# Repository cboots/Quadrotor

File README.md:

Quadrotor
======

This project contains all the schematics, code, documentation and CAD files for my quadrotor designs.

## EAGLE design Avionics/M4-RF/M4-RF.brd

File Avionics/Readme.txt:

This folder holds all of the electronics designs for the quads

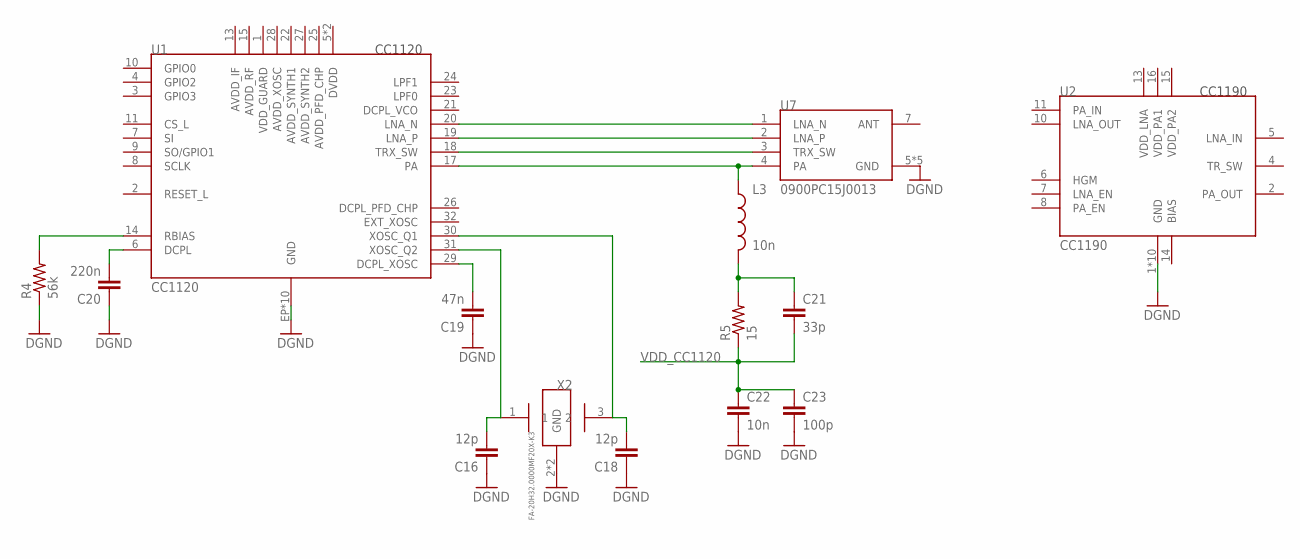
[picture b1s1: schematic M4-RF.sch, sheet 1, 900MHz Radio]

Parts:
C16, C18: 12p; 0402-CAP
C19: 47n; 0402-CAP
C20: 220n; 0402-CAP
C21: 33p; 0402-CAP
C22: 10n; 0402-CAP
C23: 100p; 0402-CAP
L3: 10n; C0402
R4: 56k; 0402-RES
R5: 15; 0402-RES
U1: CC1120; RHB_S-PVQFN-N32
U2: CC1190; RGV_S-PVQFN-N16
U7: 0900PC15J0013
X2: FA-20H32.0000MF20X-K3; FA-20H

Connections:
GND: C16.1, C18.1, C19.1, C20.1, C22.2, C23.2, R4.1, U1.EP (GND), U1.EXP@1 (GND), U1.EXP@2 (GND), U1.EXP@3 (GND), U1.EXP@4 (GND), U1.EXP@5 (GND), U1.EXP@6 (GND), U1.EXP@7 (GND), U1.EXP@8 (GND), U1.EXP@9 (GND), U2.1 (GND), U2.3 (GND), U2.9 (GND), U2.12 (GND), U2.EP (GND), U2.EP@1 (GND), U2.EP@2 (GND), U2.EP@3 (GND), U2.EP@4 (GND), U2.EP@5 (GND), U7.5 (GND), U7.6 (GND), U7.8 (GND), U7.9 (GND), U7.10 (GND), X2.2 (GND), X2.4 (GND); also elsewhere on the board
unnamed: C16.2, U1.31 (XOSC_Q2), X2.1
unnamed: C18.2, U1.30 (XOSC_Q1), X2.3 (2)
unnamed: C19.2, U1.29 (DCPL_XOSC)
unnamed: C20.2, U1.6 (DCPL)
unnamed: R4.2, U1.14 (RBIAS)
unnamed: U1.20 (LNA_N), U7.1 (LNA_N)
unnamed: U1.19 (LNA_P), U7.2 (LNA_P)
unnamed: U1.18 (TRX_SW), U7.3 (TRX_SW)
unnamed: L3.1, U1.17 (PA), U7.4 (PA)
unnamed: C21.1, L3.2, R5.2
VDD_CC1120: C21.2, C22.1, C23.1, R5.1

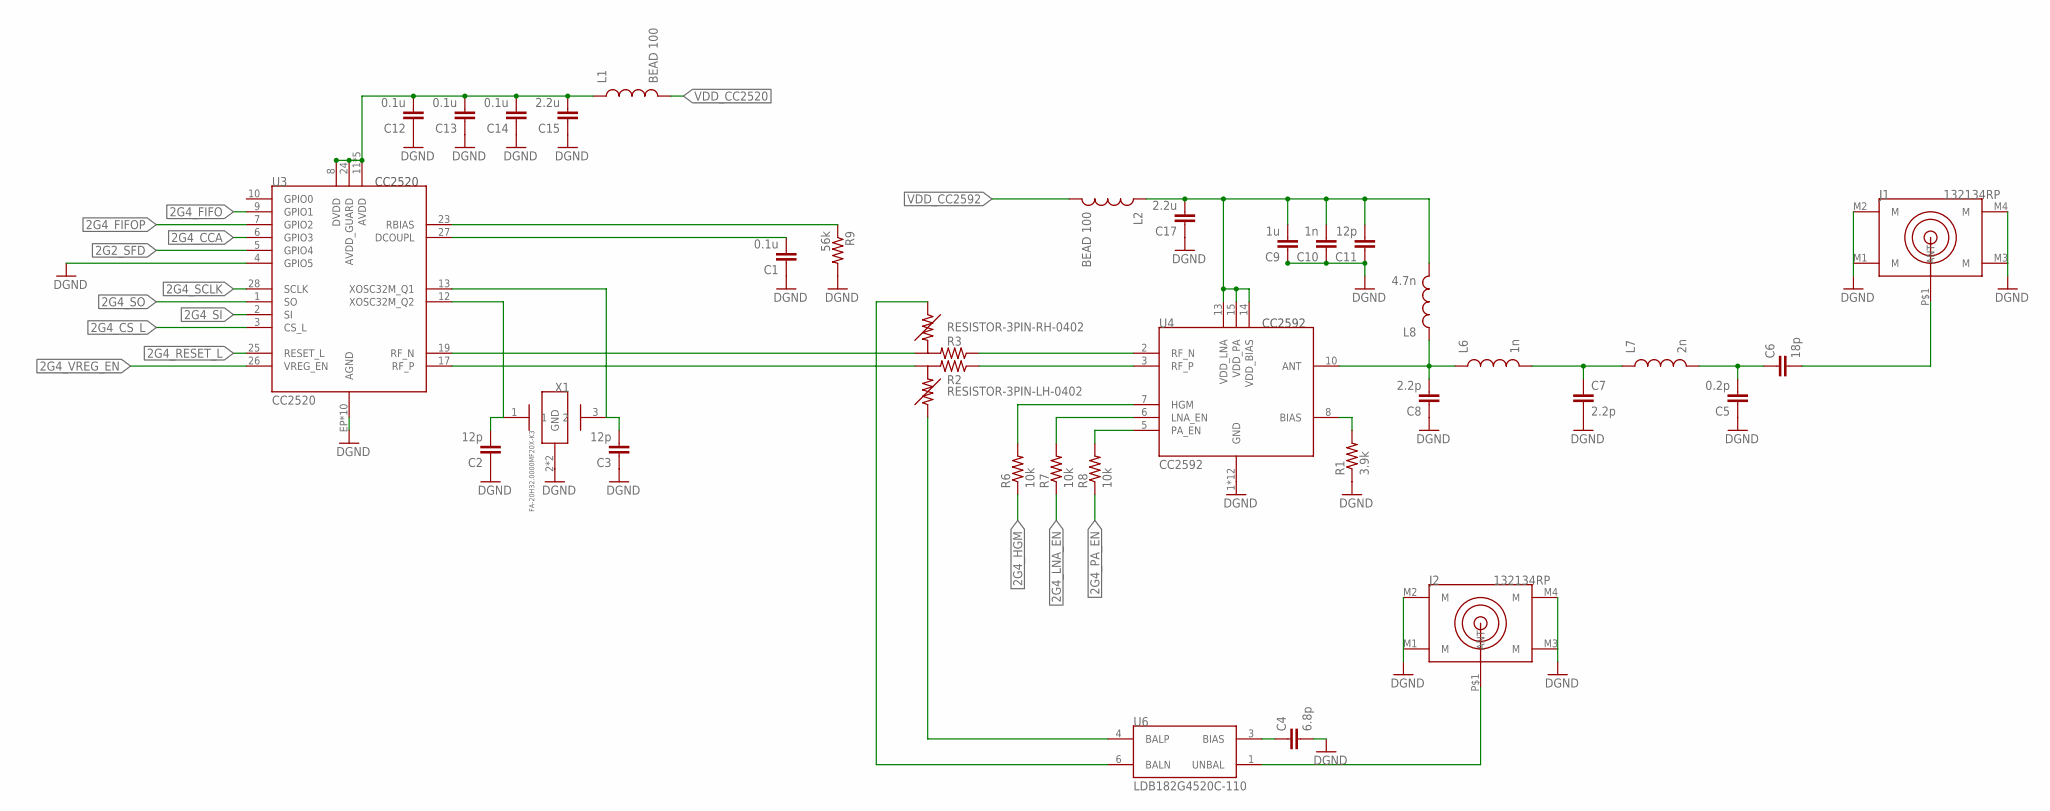
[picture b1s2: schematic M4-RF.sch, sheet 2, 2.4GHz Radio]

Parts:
C1, C12, C13, C14: 0.1u; 0402-CAP
C2, C3, C11: 12p; 0402-CAP
C4: 6.8p; 0402-CAP
C5: 0.2p; 0402-CAP
C6: 18p; 0402-CAP
C7, C8: 2.2p; 0402-CAP
C9: 1u; 0402-CAP
C10: 1n; 0402-CAP
C15, C17: 2.2u; 0402-CAP
J1, J2: 132134RP; RP-SMA-TH
L1, L2: BEAD 100; C0402
L6: 1n; C0402
L7: 2n; C0402
L8: 4.7n; C0402
R1: 3.9k; 0402-RES
R2: RESISTOR-3PIN-LH-0402; 0402-RES-3PIN-LH
R3: RESISTOR-3PIN-RH-0402; 0402-RES-3PIN-RH
R6, R7, R8: 10k; 0402-RES
R9: 56k; 0402-RES
U3: CC2520; RHD_S-PVQFN-N28
U4: CC2592; RGV_S-PVQFN-N16
U6: LDB182G4520C-110; LDB18
X1: FA-20H32.0000MF20X-K3; FA-20H

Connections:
2G2_SFD: U3.5 (GPIO4)
2G4_CCA: U3.6 (GPIO3)
2G4_CS_L: U3.3 (CS_L)
2G4_FIFO: U3.9 (GPIO1)
2G4_FIFOP: U3.7 (GPIO2)
2G4_HGM: R6.1
2G4_LG: C6.2, J1.P$1 (ANT)
2G4_LNA_EN: R7.1
2G4_LP: J2.P$1 (ANT), U6.1 (UNBAL)
2G4_PA_EN: R8.1
2G4_RESET_L: U3.25 (RESET_L)
2G4_SCLK: U3.28 (SCLK)
2G4_SI: U3.2 (SI)
2G4_SO: U3.1 (SO)
2G4_VREG_EN: U3.26 (VREG_EN)
GND: C1.1, C2.1, C3.1, C4.2, C5.1, C7.2, C8.1, C9.1, C10.1, C11.1, C12.1, C13.1, C14.1, C15.1, C17.1, J1.M1 (M), J1.M2 (M), J1.M3 (M), J1.M4 (M), J2.M1 (M), J2.M2 (M), J2.M3 (M), J2.M4 (M), R1.1, R9.2, U3.4 (GPIO5), U3.EP (AGND), U3.EXP@1 (AGND), U3.EXP@2 (AGND), U3.EXP@3 (AGND), U3.EXP@4 (AGND), U3.EXP@5 (AGND), U3.EXP@6 (AGND), U3.EXP@7 (AGND), U3.EXP@8 (AGND), U3.EXP@9 (AGND), U4.1 (GND), U4.4 (GND), U4.9 (GND), U4.11 (GND), U4.12 (GND), U4.16 (GND), U4.EP (GND), U4.EP@1 (GND), U4.EP@2 (GND), U4.EP@3 (GND), U4.EP@4 (GND), U4.EP@5 (GND), X1.2 (GND), X1.4 (GND); also elsewhere on the board
unnamed: R3.2, U3.19 (RF_N)
unnamed: R2.2, U3.17 (RF_P)
unnamed: R6.2, U4.7 (HGM)
unnamed: R7.2, U4.6 (LNA_EN)
unnamed: R2.1, U4.3 (RF_P)
unnamed: C8.2, L6.1, L8.1, U4.10 (ANT)
unnamed: C7.1, L6.2, L7.1
unnamed: C5.2, C6.1, L7.2
unnamed: C9.2, C10.2, C11.2, C17.2, L2.1, L8.2, U4.13 (VDD_LNA), U4.14 (VDD_BIAS), U4.15 (VDD_PA)
unnamed: R1.2, U4.8 (BIAS)
unnamed: R3.1, U4.2 (RF_N)
unnamed: R8.2, U4.5 (PA_EN)
unnamed: C12.2, C13.2, C14.2, C15.2, L1.1, U3.8 (DVDD), U3.11 (AVDD), U3.14 (AVDD), U3.16 (AVDD), U3.20 (AVDD), U3.22 (AVDD), U3.24 (AVDD_GUARD)
unnamed: C2.2, U3.12 (XOSC32M_Q2), X1.1
unnamed: R9.1, U3.23 (RBIAS)
unnamed: C1.2, U3.27 (DCOUPL)
unnamed: C3.2, U3.13 (XOSC32M_Q1), X1.3 (2)
unnamed: R2.3, U6.4 (BALP)
unnamed: R3.3, U6.6 (BALN)
unnamed: C4.1, U6.3 (BIAS)
VDD_CC2520: L1.2
VDD_CC2592: L2.2

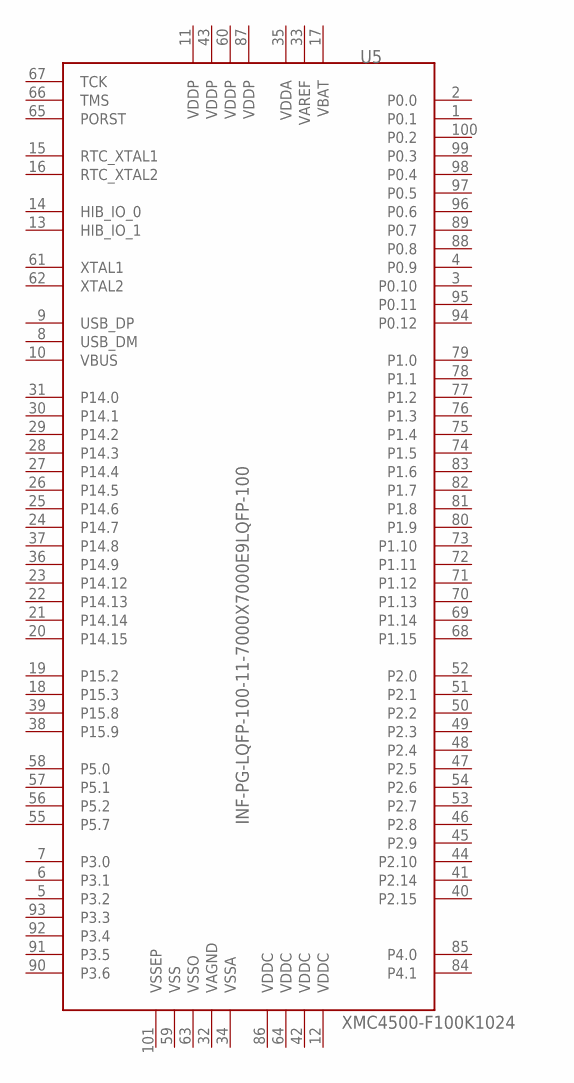
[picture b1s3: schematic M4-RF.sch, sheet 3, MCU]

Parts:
U5: INF-PG-LQFP-100-11-7000X7000E9LQFP-100; INF-PG-LQFP-100-11-7000X7000E9PRIMARY

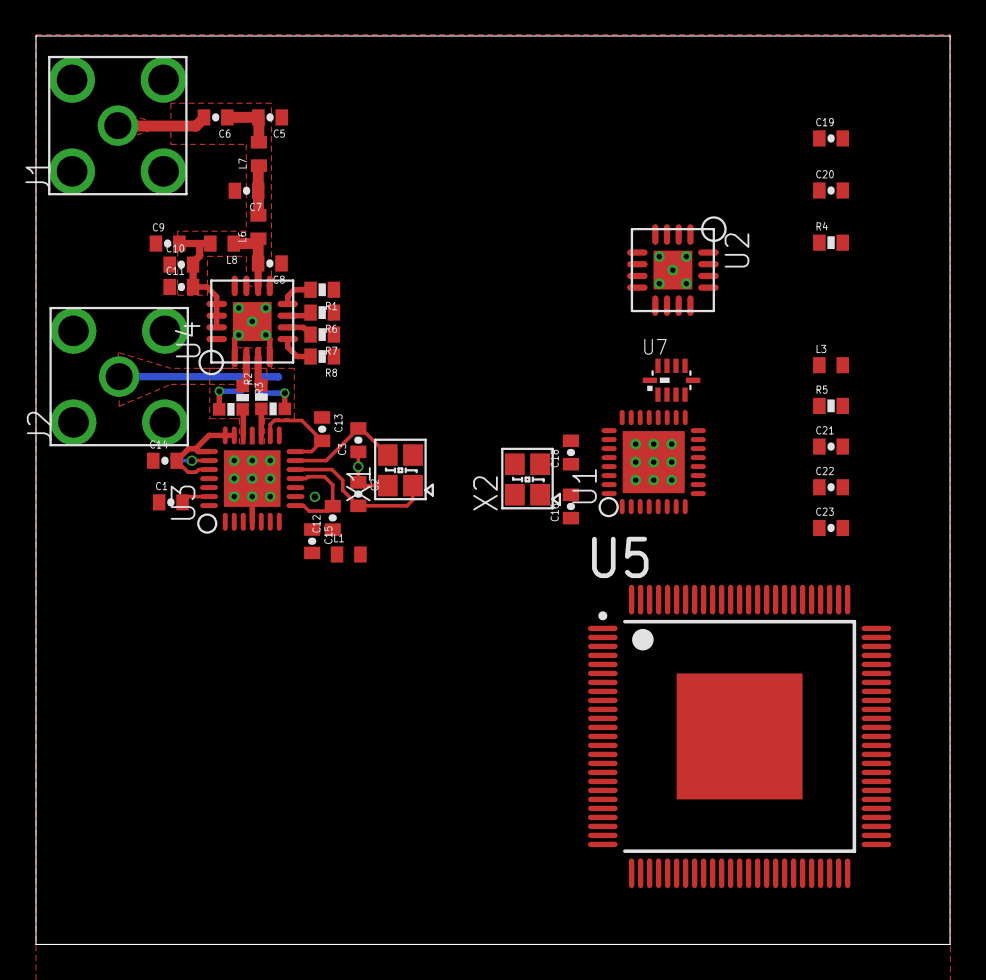
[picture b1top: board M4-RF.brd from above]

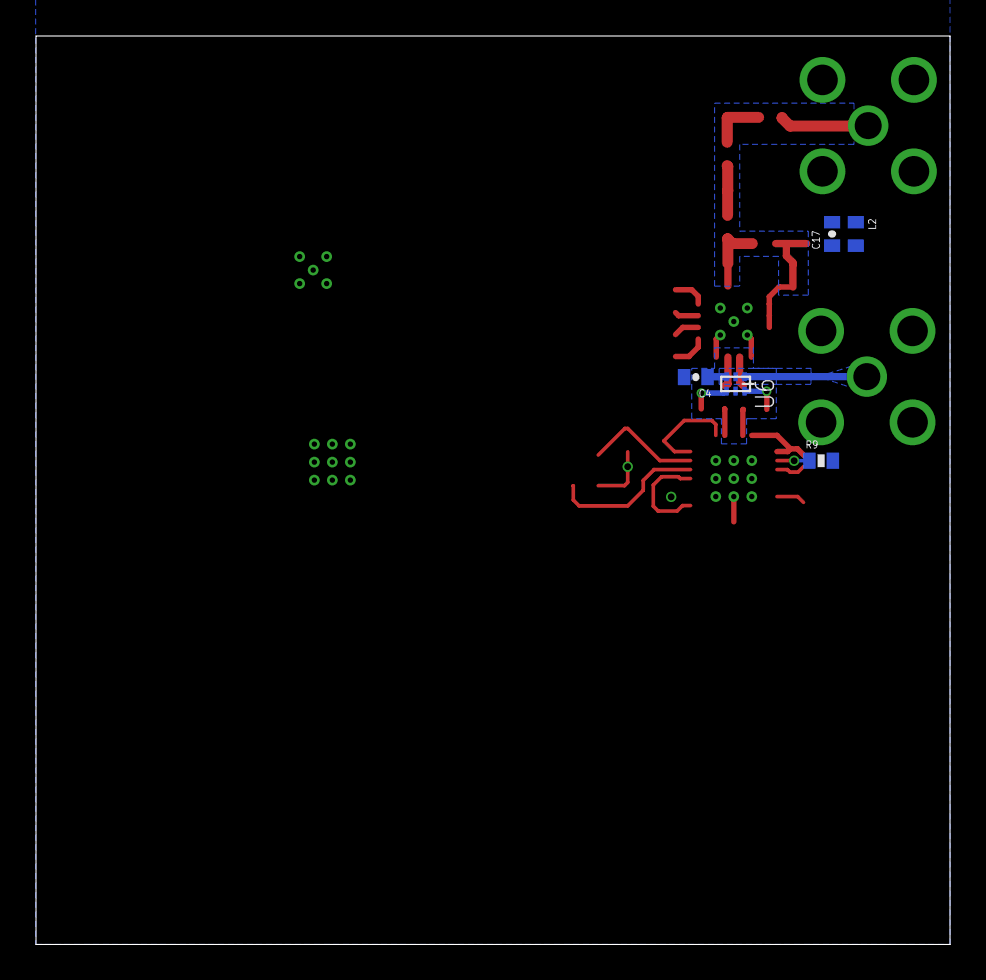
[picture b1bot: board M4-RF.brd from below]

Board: 4 copper layers, 50.8 x 50.5 mm, 49 parts (5 on the bottom side), 34 nets.

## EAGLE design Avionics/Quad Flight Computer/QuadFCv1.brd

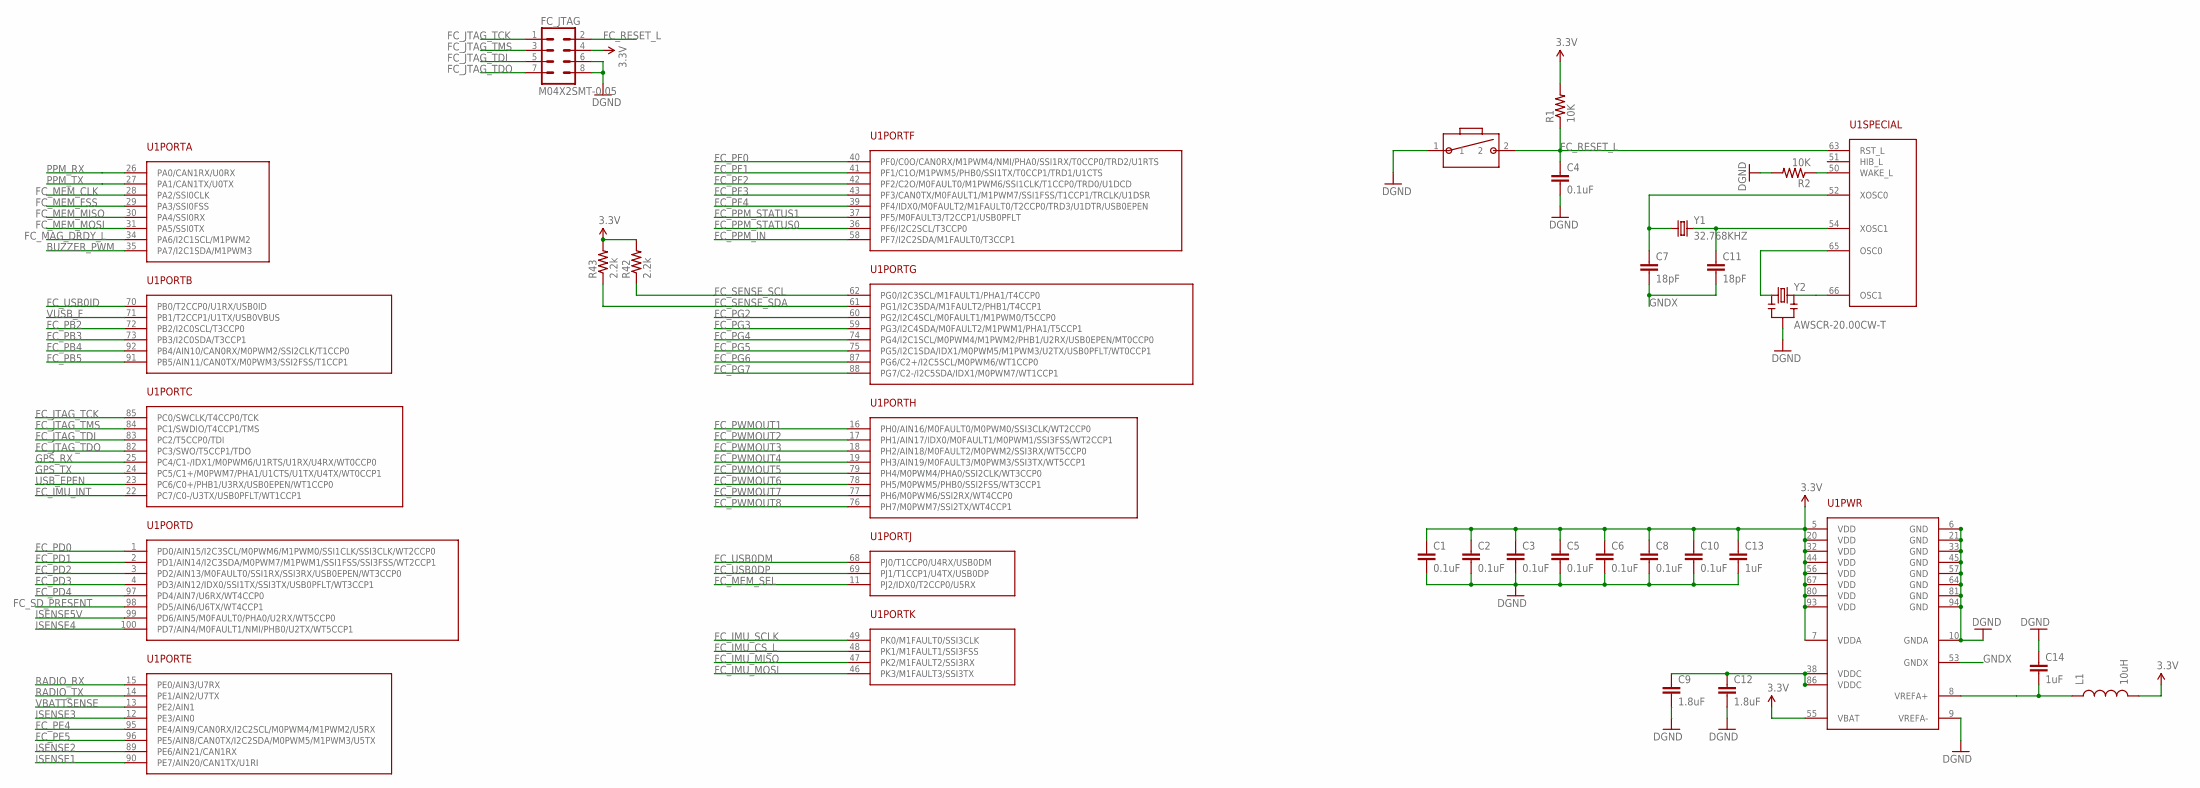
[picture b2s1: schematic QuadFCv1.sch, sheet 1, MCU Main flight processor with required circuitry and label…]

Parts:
C1, C2, C3, C4, C5, C6, C8, C10: 0.1uF; 0402-CAP
C7, C11: 18pF; 0402-CAP
C9, C12: 1.8uF; 0402-CAP
C13, C14: 1uF; 0402-CAP
FC_JTAG: M04X2SMT-0.05; 2X4_SMT-0.05
L1: 10uH; 0603
R1, R2: 10K; 0402-RES
R42, R43: 2.2k; 0402-RES
SW1: PTS635VL31-VERT; PTS635VL31
U1: TM4C123GH6PZ; LQFP100
Y1: 32.768KHZ; ECS-.327-12.5-34B
Y2: AWSCR-20.00CW-T; AWSCR-CW

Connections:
3.3V: C1.1, C2.1, C3.1, C5.1, C6.1, C8.1, C10.1, C13.1, FC_JTAG.4, L1.2, R1.2, R42.2, R43.2, U1.5 (VDD), U1.7 (VDDA), U1.20 (VDD), U1.32 (VDD), U1.44 (VDD), U1.55 (VBAT), U1.56 (VDD), U1.67 (VDD), U1.80 (VDD), U1.93 (VDD); also elsewhere on the board
BUZZER_PWM: U1.35 (PA7/I2C1SDA/M1PWM3); also elsewhere on the board
FC_IMU_CS_L: U1.48 (PK1/M1FAULT1/SSI3FSS); also elsewhere on the board
FC_IMU_INT: U1.22 (PC7/C0-/U3TX/USB0PFLT/WT1CCP1); also elsewhere on the board
FC_IMU_MISO: U1.47 (PK2/M1FAULT2/SSI3RX); also elsewhere on the board
FC_IMU_MOSI: U1.46 (PK3/M1FAULT3/SSI3TX); also elsewhere on the board
FC_IMU_SCLK: U1.49 (PK0/M1FAULT0/SSI3CLK); also elsewhere on the board
FC_JTAG_TCK: FC_JTAG.1, U1.85 (PC0/SWCLK/T4CCP0/TCK); also elsewhere on the board
FC_JTAG_TDI: FC_JTAG.5, U1.83 (PC2/T5CCP0/TDI); also elsewhere on the board
FC_JTAG_TDO: FC_JTAG.7, U1.82 (PC3/SWO/T5CCP1/TDO); also elsewhere on the board
FC_JTAG_TMS: FC_JTAG.3, U1.84 (PC1/SWDIO/T4CCP1/TMS); also elsewhere on the board
FC_MAG_DRDY_L: U1.34 (PA6/I2C1SCL/M1PWM2); also elsewhere on the board
FC_MEM_CLK: U1.28 (PA2/SSI0CLK); also elsewhere on the board
FC_MEM_FSS: U1.29 (PA3/SSI0FSS); also elsewhere on the board
FC_MEM_MISO: U1.30 (PA4/SSI0RX); also elsewhere on the board
FC_MEM_MOSI: U1.31 (PA5/SSI0TX); also elsewhere on the board
FC_MEM_SEL: U1.11 (PJ2/IDX0/T2CCP0/U5RX); also elsewhere on the board
FC_PB2: U1.72 (PB2/I2C0SCL/T3CCP0); also elsewhere on the board
FC_PB3: U1.73 (PB3/I2C0SDA/T3CCP1); also elsewhere on the board
FC_PB4: U1.92 (PB4/AIN10/CAN0RX/M0PWM2/SSI2CLK/T1CCP0); also elsewhere on the board
FC_PB5: U1.91 (PB5/AIN11/CAN0TX/M0PWM3/SSI2FSS/T1CCP1); also elsewhere on the board
FC_PD0: U1.1 (PD0/AIN15/I2C3SCL/M0PWM6/M1PWM0/SSI1CLK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); also elsewhere on the board
FC_PD1: U1.2 (PD1/AIN14/I2C3SDA/M0PWM7/M1PWM1/SSI1FSS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); also elsewhere on the board
FC_PD2: U1.3 (PD2/AIN13/M0FAULT0/SSI1RX/SSI3RX/USB0EP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); also elsewhere on the board
FC_PD3: U1.4 (PD3/AIN12/IDX0/SSI1TX/SSI3TX/USB0PFLT/W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); also elsewhere on the board
FC_PD4: U1.97 (PD4/AIN7/U6RX/WT4CCP0); also elsewhere on the board
FC_PE4: U1.95 (PE4/AIN9/CAN0RX/I2C2SCL/M0PWM4/M1PWM2/U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); also elsewhere on the board
FC_PE5: U1.96 (PE5/AIN8/CAN0TX/I2C2SDA/M0PWM5/M1PWM3/U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); also elsewhere on the board
FC_PF0: U1.40 (PF0/C0O/CAN0RX/M1PWM4/NMI/PHA0/SSI1RX/T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); also elsewhere on the board
FC_PF1: U1.41 (PF1/C1O/M1PWM5/PHB0/SSI1TX/T0CCP1/TRD1/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); also elsewhere on the board
FC_PF2: U1.42 (PF2/C2O/M0FAULT0/M1PWM6/SSI1CLK/T1CCP0/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); also elsewhere on the board
FC_PF3: U1.43 (PF3/CAN0TX/M0FAULT1/M1PWM7/SSI1FSS/T1CC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); also elsewhere on the board
FC_PF4: U1.39 (PF4/IDX0/M0FAULT2/M1FAULT0/T2CCP0/TRD3/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); also elsewhere on the board
FC_PG2: U1.60 (PG2/I2C4SCL/M0FAULT1/M1PWM0/T5CCP0); also elsewhere on the board
FC_PG3: U1.59 (PG3/I2C4SDA/M0FAULT2/M1PWM1/PHA1/T5CCP1); also elsewhere on the board
FC_PG4: U1.74 (PG4/I2C1SCL/M0PWM4/M1PWM2/PHB1/U2RX/USB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); also elsewhere on the board
FC_PG5: U1.75 (PG5/I2C1SDA/IDX1/M0PWM5/M1PWM3/U2TX/USB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); also elsewhere on the board
FC_PG6: U1.87 (PG6/C2+/I2C5SCL/M0PWM6/WT1CCP0); also elsewhere on the board
FC_PG7: U1.88 (PG7/C2-/I2C5SDA/IDX1/M0PWM7/WT1CCP1); also elsewhere on the board
FC_PPM_IN: U1.58 (PF7/I2C2SDA/M1FAULT0/T3CCP1); also elsewhere on the board
FC_PPM_STATUS0: U1.36 (PF6/I2C2SCL/T3CCP0); also elsewhere on the board
FC_PPM_STATUS1: U1.37 (PF5/M0FAULT3/T2CCP1/USB0PFLT); also elsewhere on the board
FC_PWMOUT1: U1.16 (PH0/AIN16/M0FAULT0/M0PWM0/SSI3CLK/WT2CC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); also elsewhere on the board
FC_PWMOUT2: U1.17 (PH1/AIN17/IDX0/M0FAULT1/M0PWM1/SSI3FSS/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); also elsewhere on the board
FC_PWMOUT3: U1.18 (PH2/AIN18/M0FAULT2/M0PWM2/SSI3RX/WT5CCP0); also elsewhere on the board
FC_PWMOUT4: U1.19 (PH3/AIN19/M0FAULT3/M0PWM3/SSI3TX/WT5CCP1); also elsewhere on the board
FC_PWMOUT5: U1.79 (PH4/M0PWM4/PHA0/SSI2CLK/WT3CCP0); also elsewhere on the board
FC_PWMOUT6: U1.78 (PH5/M0PWM5/PHB0/SSI2FSS/WT3CCP1); also elsewhere on the board
FC_PWMOUT7: U1.77 (PH6/M0PWM6/SSI2RX/WT4CCP0); also elsewhere on the board
FC_PWMOUT8: U1.76 (PH7/M0PWM7/SSI2TX/WT4CCP1); also elsewhere on the board
FC_RESET_L: C4.1, FC_JTAG.2, R1.1, SW1.2, U1.63 (RST_L); also elsewhere on the board
FC_SD_PRESENT: U1.98 (PD5/AIN6/U6TX/WT4CCP1); also elsewhere on the board
FC_SENSE_SCL: R42.1, U1.62 (PG0/I2C3SCL/M1FAULT1/PHA1/T4CCP0); also elsewhere on the board
FC_SENSE_SDA: R43.1, U1.61 (PG1/I2C3SDA/M1FAULT2/PHB1/T4CCP1); also elsewhere on the board
FC_USB0DM: U1.68 (PJ0/T1CCP0/U4RX/USB0DM); also elsewhere on the board
FC_USB0DP: U1.69 (PJ1/T1CCP1/U4TX/USB0DP); also elsewhere on the board
FC_USB0ID: U1.70 (PB0/T2CCP0/U1RX/USB0ID); also elsewhere on the board
GND: C1.2, C2.2, C3.2, C4.2, C5.2, C6.2, C8.2, C9.2, C10.2, C12.2, C13.2, C14.1, FC_JTAG.6, FC_JTAG.8, R2.2, SW1.1, U1.6 (GND), U1.9 (VREFA-), U1.10 (GNDA), U1.21 (GND), U1.33 (GND), U1.45 (GND), U1.57 (GND), U1.64 (GND), U1.81 (GND), U1.94 (GND), Y2.P$2 (2); also elsewhere on the board
GNDX: C7.2, C11.2, U1.53 (GNDX)
GPS_RX: U1.25 (PC4/C1-/IDX1/M0PWM6/U1RTS/U1RX/U4RX/WT0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); also elsewhere on the board
GPS_TX: U1.24 (PC5/C1+/M0PWM7/PHA1/U1CTS/U1TX/U4TX/WT0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); also elsewhere on the board
ISENSE1: U1.90 (PE7/AIN20/CAN1TX/U1RI); also elsewhere on the board
ISENSE2: U1.89 (PE6/AIN21/CAN1RX); also elsewhere on the board
ISENSE3: U1.12 (PE3/AIN0); also elsewhere on the board
ISENSE4: U1.100 (PD7/AIN4/M0FAULT1/NMI/PHB0/U2TX/WT5CCP1); also elsewhere on the board
ISENSE5V: U1.99 (PD6/AIN5/M0FAULT0/PHA0/U2RX/WT5CCP0); also elsewhere on the board
unnamed: C14.2, L1.1, U1.8 (VREFA+)
unnamed: C9.1, C12.1, U1.38 (VDDC), U1.86 (VDDC)
unnamed: C11.1, U1.54 (XOSC1), Y1.P$2 (2)
unnamed: C7.1, U1.52 (XOSC0), Y1.P$1 (1)
unnamed: R2.1, U1.50 (WAKE_L)
unnamed: U1.65 (OSC0), Y2.P$1 (1)
unnamed: U1.66 (OSC1), Y2.P$3 (3)
PPM_RX: U1.26 (PA0/CAN1RX/U0RX); also elsewhere on the board
PPM_TX: U1.27 (PA1/CAN1TX/U0TX); also elsewhere on the board
RADIO_RX: U1.15 (PE0/AIN3/U7RX); also elsewhere on the board
RADIO_TX: U1.14 (PE1/AIN2/U7TX); also elsewhere on the board
USB_EPEN: U1.23 (PC6/C0+/PHB1/U3RX/USB0EPEN/WT1CCP0); also elsewhere on the board
VBATTSENSE: U1.13 (PE2/AIN1); also elsewhere on the board
VUSB_F: U1.71 (PB1/T2CCP1/U1TX/USB0VBUS); also elsewhere on the board

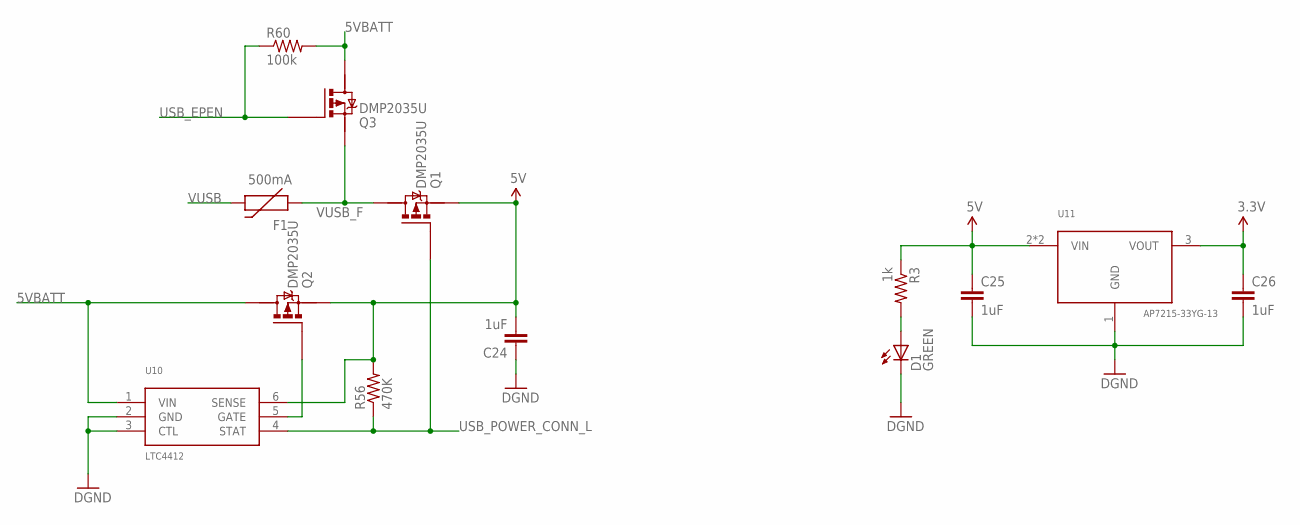
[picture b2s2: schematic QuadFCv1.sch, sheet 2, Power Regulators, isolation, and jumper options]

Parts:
C24, C25, C26: 1uF; 0402-CAP
D1: GREEN; LED-0603
F1: 500mA; PTC-1206
Q1, Q2, Q3: DMP2035U; SOT23
R3: 1k; 0402-RES
R56: 470K; 0402-RES
R60: 100k; 0402-RES
U10: LTC4412; SOT23-6
U11: AP7215-33YG-13; SOT89

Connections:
3.3V: C26.1, U11.3 (VOUT); also elsewhere on the board
5V: C24.2, C25.1, Q1.2 (S), Q2.2 (S), R3.1, R56.2, U10.6 (SENSE), U11.2 (VIN), U11.2@1 (VIN); also elsewhere on the board
5VBATT: Q2.3 (D), Q3.3 (D), R60.2, U10.1 (VIN); also elsewhere on the board
GND: C24.1, C25.2, C26.2, D1.C, U10.2 (GND), U10.3 (CTL), U11.1 (GND); also elsewhere on the board
unnamed: D1.A, R3.2
unnamed: Q2.1 (G), U10.5 (GATE)
USB_EPEN: Q3.1 (G), R60.1; also elsewhere on the board
USB_POWER_CONN_L: Q1.1 (G), R56.1, U10.4 (STAT)
VUSB: F1.2; also elsewhere on the board
VUSB_F: F1.1, Q1.3 (D), Q3.2 (S); also elsewhere on the board

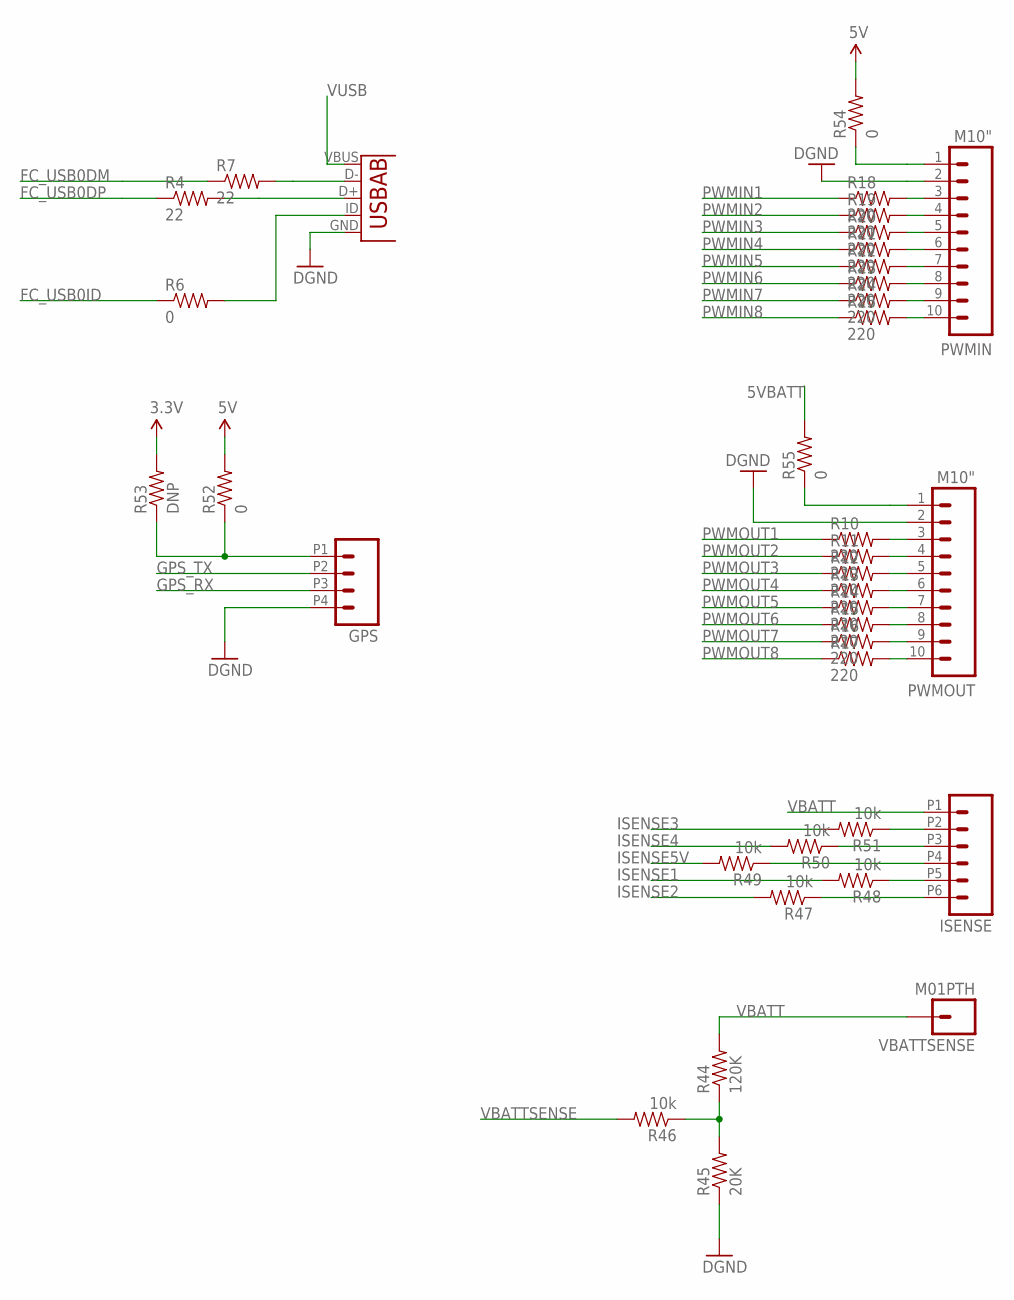
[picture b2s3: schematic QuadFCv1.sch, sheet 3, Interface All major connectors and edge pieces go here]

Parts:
GPS: M04DF13; DF13A-4P-1.25H
ISENSE: M06DF13; DF13A-6P-1.25H
PWMIN: M10"; 1X10
PWMOUT: M10"; 1X10
R4, R7: 22; 0402-RES
R6, R52: 0; 0402-RES
R10, R11, R12, R13, R14, R15, R16, R17, R18, R19, R20, R21, R22, R23, R24, R25: 220; 0402-RES
R44: 120K; 0402-RES
R45: 20K; 0402-RES
R46, R47, R48, R49, R50, R51: 10k; 0402-RES
R53: DNP; 0402-RES
R54, R55: 0; 0603-RES
U12: USB-AB; USB-AB-MICRO-SMD
VBATTSENSE: M01PTH; 1X01

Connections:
3.3V: R53.2; also elsewhere on the board
5V: R52.2, R54.2; also elsewhere on the board
5VBATT: R55.2; also elsewhere on the board
FC_USB0DM: R7.1; also elsewhere on the board
FC_USB0DP: R4.1; also elsewhere on the board
FC_USB0ID: R6.1; also elsewhere on the board
GND: GPS.P4 (4), PWMIN.2, PWMOUT.2, R45.1, U12.GND; also elsewhere on the board
GPS_RX: GPS.P3 (3); also elsewhere on the board
GPS_TX: GPS.P2 (2); also elsewhere on the board
ISENSE1: R48.2; also elsewhere on the board
ISENSE2: R47.2; also elsewhere on the board
ISENSE3: R51.2; also elsewhere on the board
ISENSE4: R50.2; also elsewhere on the board
ISENSE5V: R49.2; also elsewhere on the board
unnamed: PWMIN.3, R18.2
unnamed: PWMIN.4, R19.2
unnamed: PWMIN.5, R20.2
unnamed: PWMIN.6, R21.2
unnamed: PWMIN.7, R22.2
unnamed: PWMIN.8, R23.2
unnamed: PWMIN.9, R24.2
unnamed: PWMIN.10, R25.2
unnamed: PWMOUT.3, R10.2
unnamed: PWMOUT.4, R11.2
unnamed: PWMOUT.5, R12.2
unnamed: PWMOUT.6, R13.2
unnamed: PWMOUT.7, R14.2
unnamed: PWMOUT.8, R15.2
unnamed: PWMOUT.9, R16.2
unnamed: PWMOUT.10, R17.2
unnamed: PWMIN.1, R54.1
unnamed: PWMOUT.1, R55.1
unnamed: R6.2, U12.ID (USBID)
unnamed: R4.2, U12.D+
unnamed: ISENSE.P6 (6), R47.1
unnamed: ISENSE.P5 (5), R48.1
unnamed: R44.1, R45.2, R46.1
unnamed: GPS.P1 (1), R52.1, R53.1
unnamed: ISENSE.P4 (4), R49.1
unnamed: ISENSE.P3 (3), R50.1
unnamed: ISENSE.P2 (2), R51.1
unnamed: R7.2, U12.D-
PWMIN1: R18.1; also elsewhere on the board
PWMIN2: R19.1; also elsewhere on the board
PWMIN3: R20.1; also elsewhere on the board
PWMIN4: R21.1; also elsewhere on the board
PWMIN5: R22.1; also elsewhere on the board
PWMIN6: R23.1; also elsewhere on the board
PWMIN7: R24.1; also elsewhere on the board
PWMIN8: R25.1; also elsewhere on the board
PWMOUT1: R10.1; also elsewhere on the board
PWMOUT2: R11.1; also elsewhere on the board
PWMOUT3: R12.1; also elsewhere on the board
PWMOUT4: R13.1; also elsewhere on the board
PWMOUT5: R14.1; also elsewhere on the board
PWMOUT6: R15.1; also elsewhere on the board
PWMOUT7: R16.1; also elsewhere on the board
PWMOUT8: R17.1; also elsewhere on the board
VBATT: ISENSE.P1 (1), R44.2, VBATTSENSE.1
VBATTSENSE: R46.2; also elsewhere on the board
VUSB: U12.VBUS; also elsewhere on the board

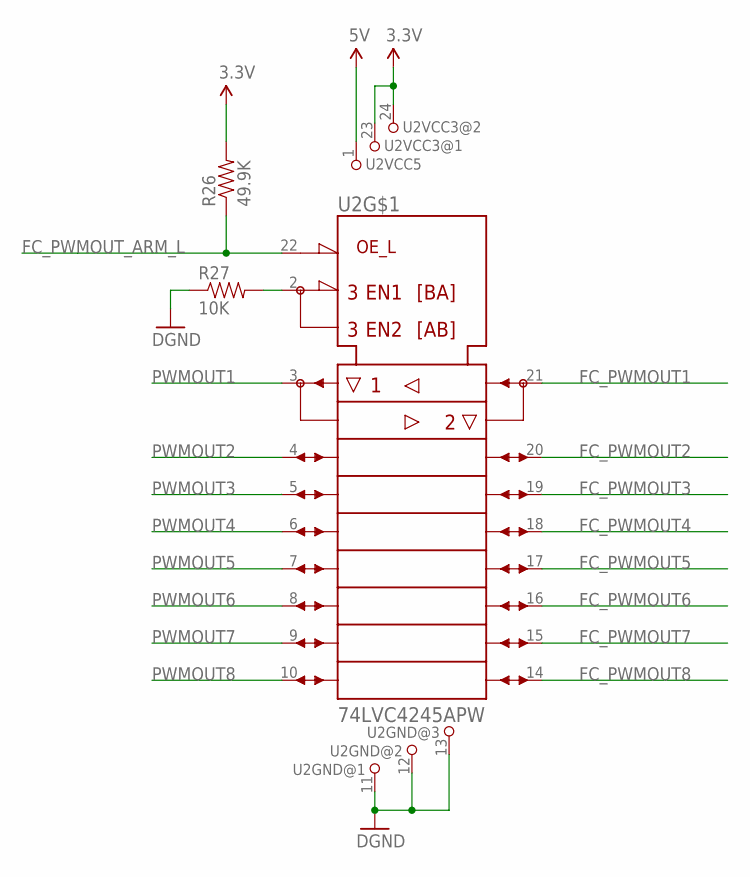
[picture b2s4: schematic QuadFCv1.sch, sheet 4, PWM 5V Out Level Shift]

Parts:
R26: 49.9K; 0402-RES
R27: 10K; 0402-RES
U2: 74LVC4245APW; TSSOP24

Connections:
3.3V: R26.2, U2.23 (1), U2.24 (1); also elsewhere on the board
5V: U2.1; also elsewhere on the board
FC_PWMOUT1: U2.21 (B1); also elsewhere on the board
FC_PWMOUT2: U2.20 (B2); also elsewhere on the board
FC_PWMOUT3: U2.19 (B3); also elsewhere on the board
FC_PWMOUT4: U2.18 (B4); also elsewhere on the board
FC_PWMOUT5: U2.17 (B5); also elsewhere on the board
FC_PWMOUT6: U2.16 (B6); also elsewhere on the board
FC_PWMOUT7: U2.15 (B7); also elsewhere on the board
FC_PWMOUT8: U2.14 (B8); also elsewhere on the board
FC_PWMOUT_ARM_L: R26.1, U2.22 (OE_L)
GND: R27.1, U2.11 (1), U2.12 (1), U2.13 (1); also elsewhere on the board
unnamed: R27.2, U2.2 (DIR)
PWMOUT1: U2.3 (A1); also elsewhere on the board
PWMOUT2: U2.4 (A2); also elsewhere on the board
PWMOUT3: U2.5 (A3); also elsewhere on the board
PWMOUT4: U2.6 (A4); also elsewhere on the board
PWMOUT5: U2.7 (A5); also elsewhere on the board
PWMOUT6: U2.8 (A6); also elsewhere on the board
PWMOUT7: U2.9 (A7); also elsewhere on the board
PWMOUT8: U2.10 (A8); also elsewhere on the board

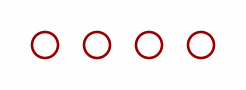
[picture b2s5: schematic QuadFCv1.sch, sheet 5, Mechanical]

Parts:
STANDOFF1, STANDOFF2, STANDOFF3, STANDOFF4: STAND-OFF

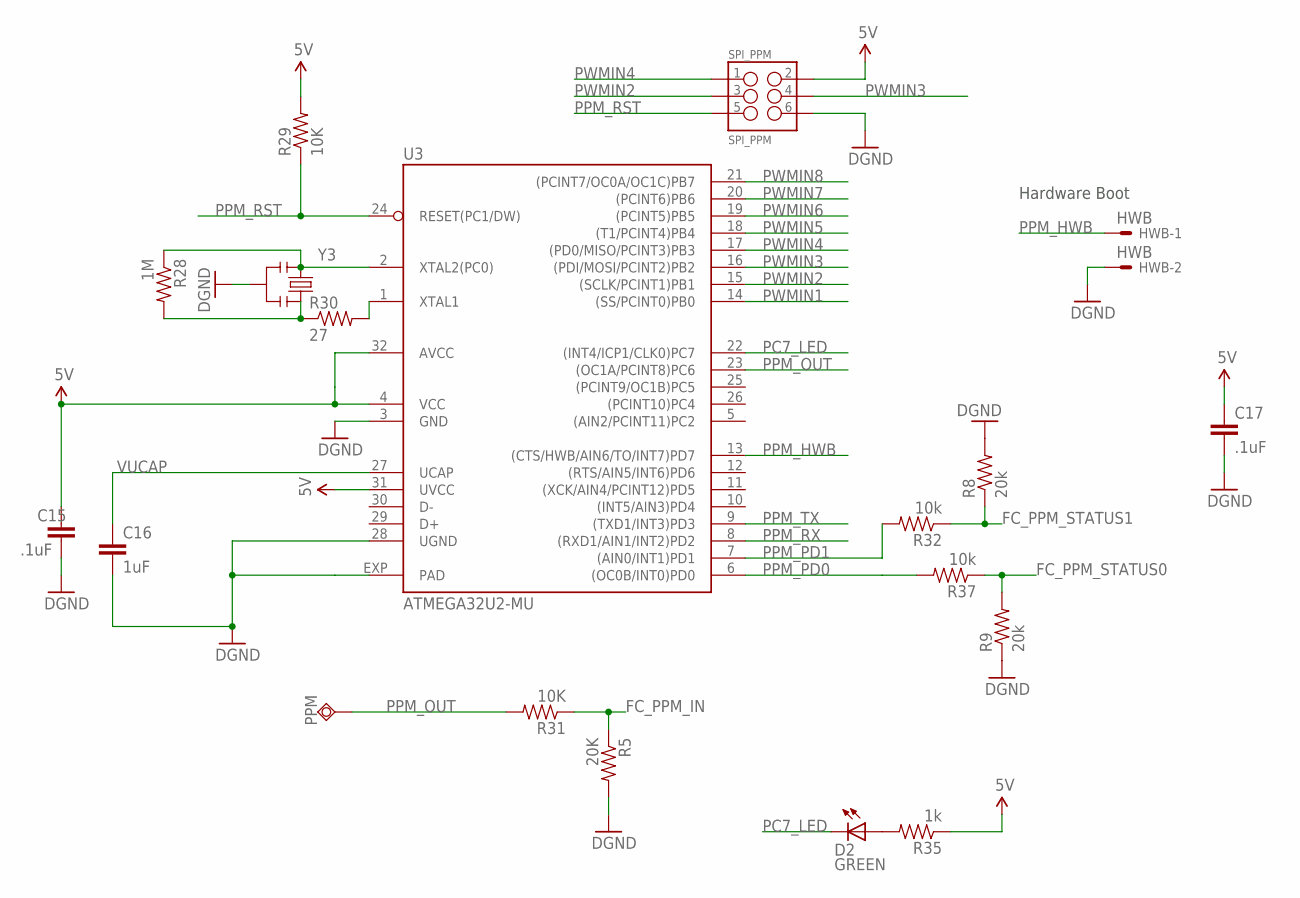
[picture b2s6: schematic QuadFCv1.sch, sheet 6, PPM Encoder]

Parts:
C15, C17: .1uF; 0402-CAP
C16: 1uF; 0402-CAP
D2: GREEN; LED-0603
HWB: HWB; 87758-0216
PPM: TESTPAD_TPSQTP10SQ; TP10SQ
R5: 20K; 0402-RES
R8, R9: 20k; 0402-RES
R28: 1M; 0402-RES
R29, R31: 10K; 0402-RES
R30: 27; 0402-RES
R32, R37: 10k; 0402-RES
R35: 1k; 0402-RES
SPI_PPM: SPI_PPM; 2X3_SMT-0.05
U3: ATMEGA32U2-MU; QFN32
Y3: PRQC16.00SR5010X000

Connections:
5V: C15.1, C17.1, R29.2, R35.1, SPI_PPM.2, U3.4 (VCC), U3.31 (UVCC), U3.32 (AVCC); also elsewhere on the board
FC_PPM_IN: R5.1, R31.1; also elsewhere on the board
FC_PPM_STATUS0: R9.2, R37.1; also elsewhere on the board
FC_PPM_STATUS1: R8.1, R32.1; also elsewhere on the board
GND: C15.2, C16.2, C17.2, HWB.2, R5.2, R8.2, R9.1, SPI_PPM.6, U3.3 (GND), U3.28 (UGND), U3.EXP (PAD), Y3.2; also elsewhere on the board
unnamed: D2.A, R35.2
PC7_LED: D2.C, U3.22 ((INT4/ICP1/CLK0)PC7)
PPM_HWB: HWB.1, U3.13 ((CTS/HWB/AIN6/TO/INT7)PD7)
PPM_OUT: PPM.TP, R31.2, U3.23 ((OC1A/PCINT8)PC6)
PPM_PD0: R37.2, U3.6 ((OC0B/INT0)PD0)
PPM_PD1: R32.2, U3.7 ((AIN0/INT1)PD1)
PPM_RST: R29.1, SPI_PPM.5, U3.24 (RESET(PC1/DW))
PPM_RX: U3.8 ((RXD1/AIN1/INT2)PD2); also elsewhere on the board
PPM_TX: U3.9 ((TXD1/INT3)PD3); also elsewhere on the board
PWMIN1: U3.14 ((SS/PCINT0)PB0); also elsewhere on the board
PWMIN2: SPI_PPM.3, U3.15 ((SCLK/PCINT1)PB1); also elsewhere on the board
PWMIN3: SPI_PPM.4, U3.16 ((PDI/MOSI/PCINT2)PB2); also elsewhere on the board
PWMIN4: SPI_PPM.1, U3.17 ((PD0/MISO/PCINT3)PB3); also elsewhere on the board
PWMIN5: U3.18 ((T1/PCINT4)PB4); also elsewhere on the board
PWMIN6: U3.19 ((PCINT5)PB5); also elsewhere on the board
PWMIN7: U3.20 ((PCINT6)PB6); also elsewhere on the board
PWMIN8: U3.21 ((PCINT7/OC0A/OC1C)PB7); also elsewhere on the board
VUCAP: C16.1, U3.27 (UCAP)
XT1: R28.2, R30.1, Y3.3
XT1R: R30.2, U3.1 (XTAL1)
XT2: R28.1, U3.2 (XTAL2(PC0)), Y3.1

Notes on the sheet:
Hardware Boot

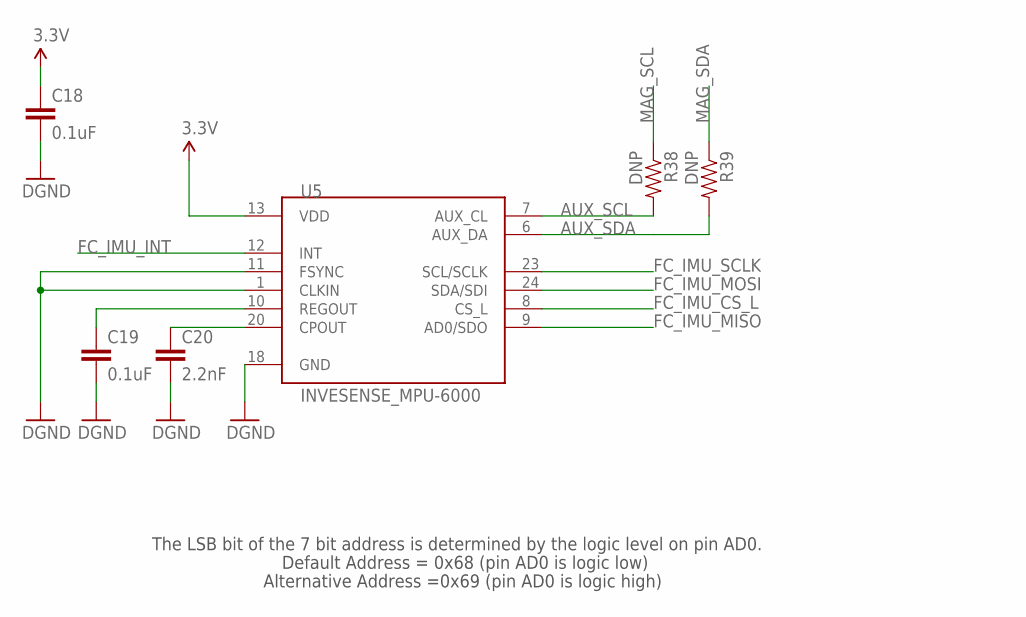
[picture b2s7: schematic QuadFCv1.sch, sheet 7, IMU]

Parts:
C18, C19: 0.1uF; 0402-CAP
C20: 2.2nF; 0402-CAP
R38, R39: DNP; 0402-RES
U5: INVESENSE_MPU-6000; QFN-24-4MM2

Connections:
3.3V: C18.1, U5.13 (VDD); also elsewhere on the board
AUX_SCL: R38.2, U5.7 (AUX_CL)
AUX_SDA: R39.2, U5.6 (AUX_DA)
FC_IMU_CS_L: U5.8 (CS_L); also elsewhere on the board
FC_IMU_INT: U5.12 (INT); also elsewhere on the board
FC_IMU_MISO: U5.9 (AD0/SDO); also elsewhere on the board
FC_IMU_MOSI: U5.24 (SDA/SDI); also elsewhere on the board
FC_IMU_SCLK: U5.23 (SCL/SCLK); also elsewhere on the board
GND: C18.2, C19.2, C20.2, U5.1 (CLKIN), U5.11 (FSYNC), U5.18 (GND); also elsewhere on the board
MAG_SCL: R38.1; also elsewhere on the board
MAG_SDA: R39.1; also elsewhere on the board
unnamed: C20.1, U5.20 (CPOUT)
unnamed: C19.1, U5.10 (REGOUT)

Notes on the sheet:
Default Address = 0x68 (pin AD0 is logic low)
Alternative Address =0x69 (pin AD0 is logic high)
The LSB bit of the 7 bit address is determined by the logic level on pin AD0.

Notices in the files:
parts and their libraries:
SparkFun-Electromechanical: Licensing: CC v3.0 Share-Alike You are welcome to use this library for commercial purposes.
